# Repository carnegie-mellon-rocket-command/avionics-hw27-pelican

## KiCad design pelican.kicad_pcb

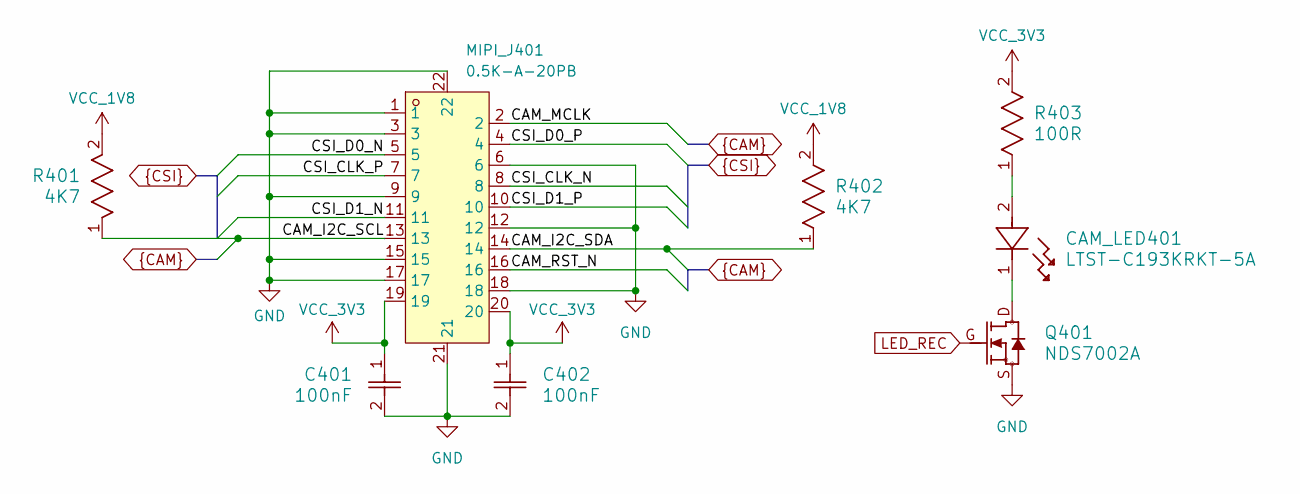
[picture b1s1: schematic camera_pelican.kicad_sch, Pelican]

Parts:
C401, C402: 100nF; C_GRM155R71C104KA88D; LCSC Part # C71629
CAM_LED401: LTST-C193KRKT-5A; LED_LTST-C193KRKT-5A; LCSC Part # C157741
MIPI_J401: 0.5K-A-20PB; J_0.5K-A-20PB; MPN 0.5K-A-20PB; LCSC Part C2914144
Q401: NDS7002A; Q_NDS7002A; LCSC Part # C74715
R401, R402: 4K7; R_RC0402FR; LCSC Part # C105871
R403: 100R; R_RC0402FR; LCSC Part # C106232

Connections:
CAM_I2C_SCL: MIPI_J401.13, R401.1; also elsewhere on the board
CAM_I2C_SDA: MIPI_J401.14, R402.1; also elsewhere on the board
CAM_MCLK: MIPI_J401.2; also elsewhere on the board
CAM_RST_N: MIPI_J401.16; also elsewhere on the board
CSI_CLK_N: MIPI_J401.8; also elsewhere on the board
CSI_CLK_P: MIPI_J401.7; also elsewhere on the board
CSI_D0_N: MIPI_J401.5; also elsewhere on the board
CSI_D0_P: MIPI_J401.4; also elsewhere on the board
CSI_D1_N: MIPI_J401.11; also elsewhere on the board
CSI_D1_P: MIPI_J401.10; also elsewhere on the board
GND: C401.2, C402.2, MIPI_J401.1, MIPI_J401.3, MIPI_J401.6, MIPI_J401.9, MIPI_J401.12, MIPI_J401.15, MIPI_J401.17, MIPI_J401.18, MIPI_J401.21, MIPI_J401.22, Q401.S; also elsewhere on the board
LED_REC: Q401.G; also elsewhere on the board
unnamed: CAM_LED401.1, Q401.D
unnamed: CAM_LED401.2, R403.1
VCC_1V8: R401.2, R402.2; also elsewhere on the board
VCC_3V3: C401.1, C402.1, MIPI_J401.19, MIPI_J401.20, R403.2; also elsewhere on the board

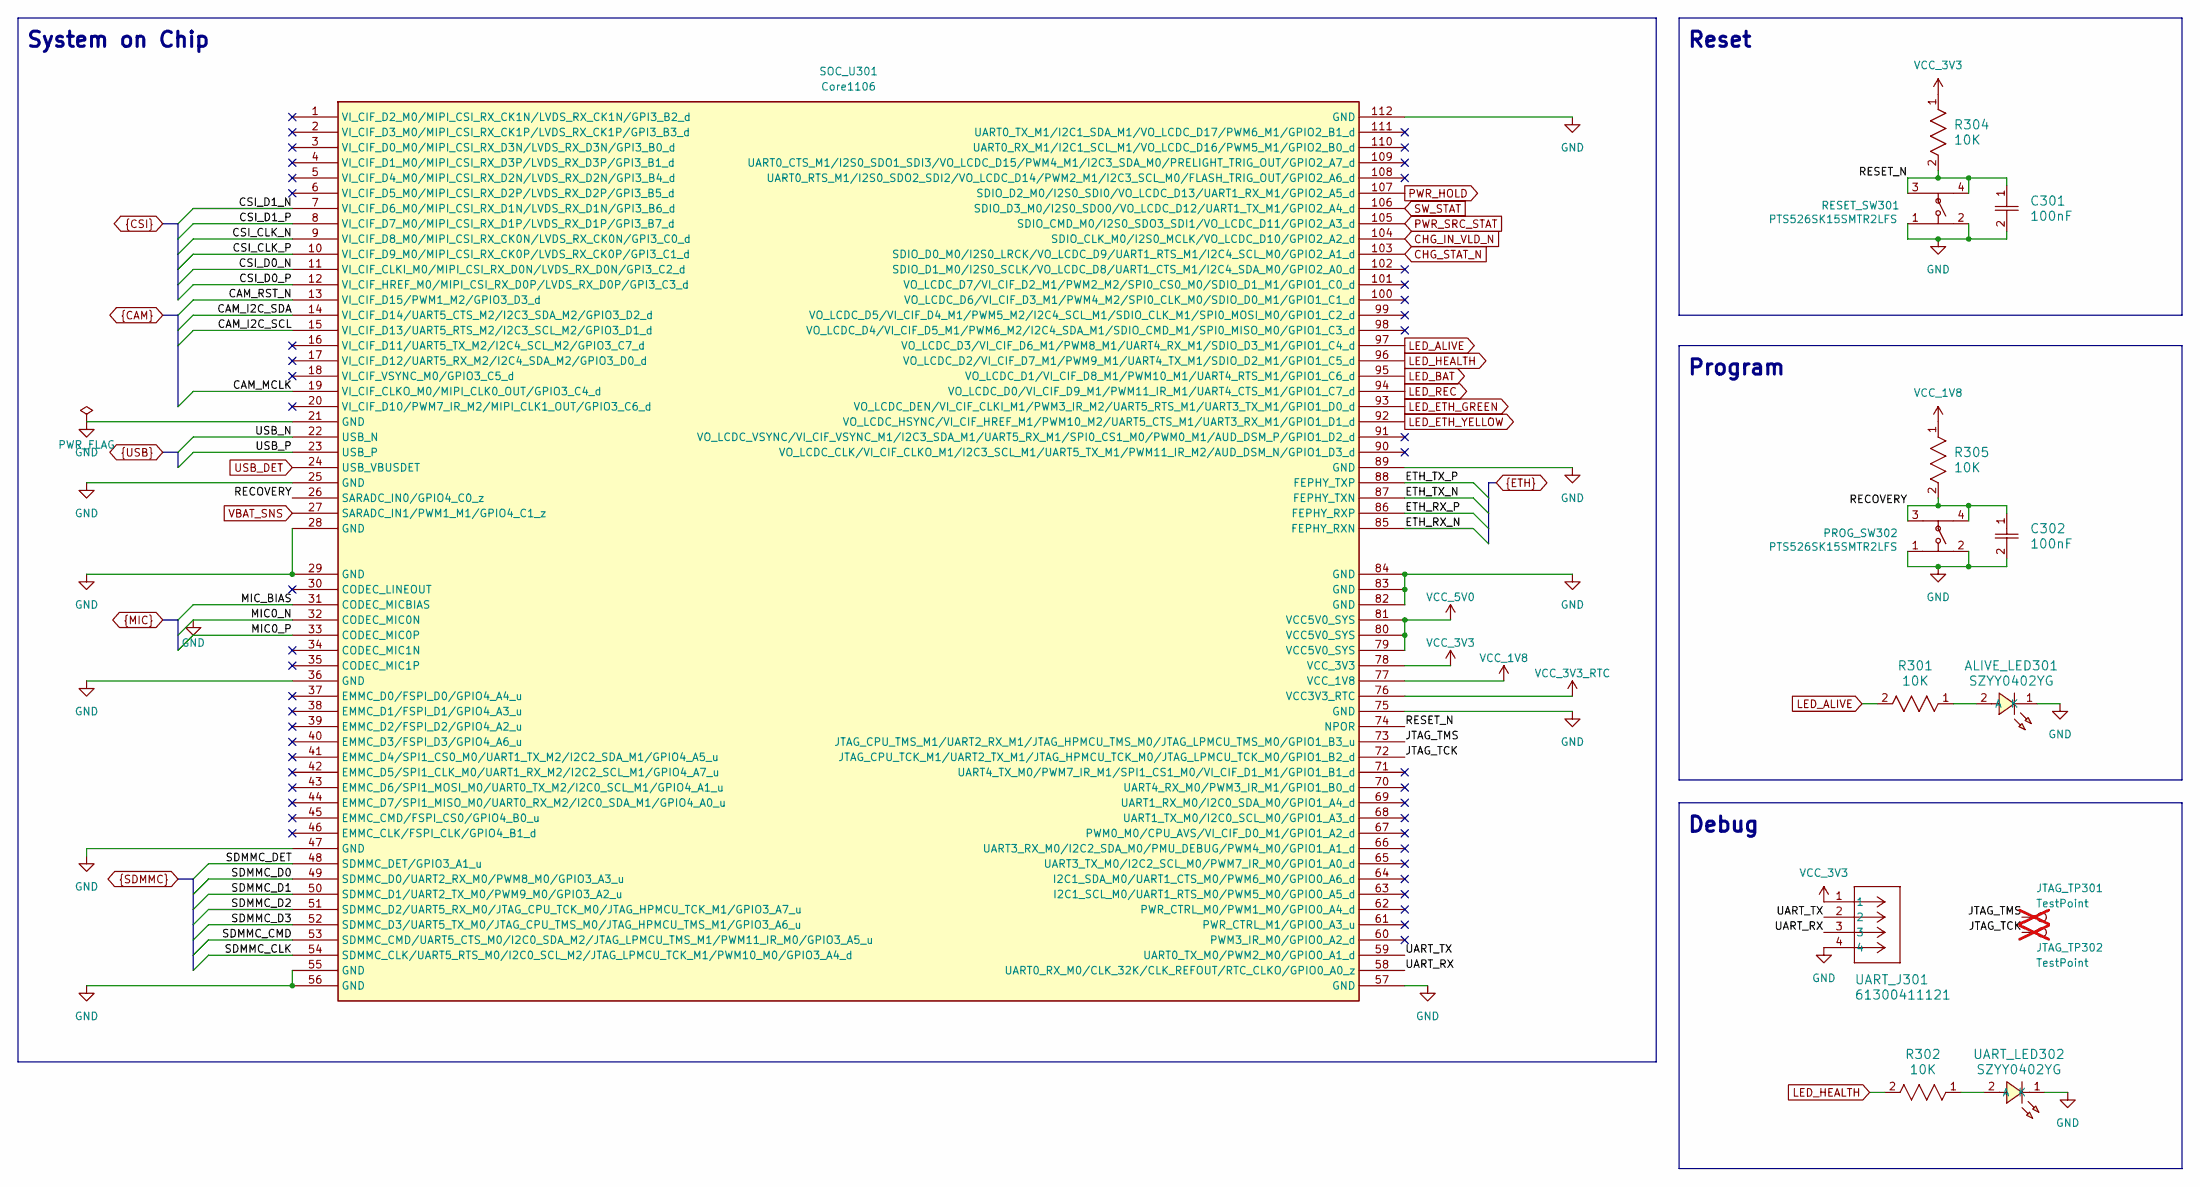
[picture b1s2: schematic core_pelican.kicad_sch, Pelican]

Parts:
ALIVE_LED301: SZYY0402YG; LED_SZYY0402YG; MPN SZYY0402YG; LCSC Part # C434449
C301, C302: 100nF; C_GRM155R71C104KA88D; LCSC Part # C71629
JTAG_TP301, JTAG_TP302: TestPoint; TestPoint_Pad_D1.5mm; not fitted
PROG_SW302: PTS526SK15SMTR2LFS; SW_PTS526SK15SMTR2LFS; LCSC Part # C2689521
R301, R302, R304, R305: 10K; R_RC0402FR; LCSC Part # C60490
RESET_SW301: PTS526SK15SMTR2LFS; SW_PTS526SK15SMTR2LFS; LCSC Part # C2689521
SOC_U301: Core1106; P_Core1106
UART_J301: 61300411121; J_61300411121; LCSC Part # C5184785
UART_LED302: SZYY0402YG; LED_SZYY0402YG; MPN SZYY0402YG; LCSC Part # C434449

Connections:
/Core/JTAG_TCK: JTAG_TP302.1 (1_1), SOC_U301.72 (JTAG_CPU_TCK_M1/UART2_TX_M1/JTAG_HPMCU_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)
/Core/JTAG_TMS: JTAG_TP301.1 (1_1), SOC_U301.73 (JTAG_CPU_TMS_M1/UART2_RX_M1/JTAG_HPMCU_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)
/Core/RECOVERY: C302.1, PROG_SW302.3, PROG_SW302.4, R305.2, SOC_U301.26 (SARADC_IN0/GPIO4_C0_z)
/Core/RESET_N: C301.1, R304.2, RESET_SW301.3, RESET_SW301.4, SOC_U301.74 (NPOR)
/Core/UART_RX: SOC_U301.58 (UART0_RX_M0/CLK_32K/CLK_REFOUT/RTC_CLKO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), UART_J301.3; also elsewhere on the board
/Core/UART_TX: SOC_U301.59 (UART0_TX_M0/PWM2_M0/GPIO0_A1_d), UART_J301.2; also elsewhere on the board
CAM_I2C_SCL: SOC_U301.15 (VI_CIF_D13/UART5_RTS_M2/I2C3_SCL_M2/GPI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); also elsewhere on the board
CAM_I2C_SDA: SOC_U301.14 (VI_CIF_D14/UART5_CTS_M2/I2C3_SDA_M2/GPI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); also elsewhere on the board
CAM_MCLK: SOC_U301.19 (VI_CIF_CLKO_M0/MIPI_CLK0_OUT/GPIO3_C4_d); also elsewhere on the board
CAM_RST_N: SOC_U301.13 (VI_CIF_D15/PWM1_M2/GPIO3_D3_d); also elsewhere on the board
CHG_IN_VLD_N: SOC_U301.104 (SDIO_CLK_M0/I2S0_MCLK/VO_LCDC_D10/GPIO2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); also elsewhere on the board
CHG_STAT_N: SOC_U301.103 (SDIO_D0_M0/I2S0_LRCK/VO_LCDC_D9/UART1_R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); also elsewhere on the board
CSI_CLK_N: SOC_U301.9 (VI_CIF_D8_M0/MIPI_CSI_RX_CK0N/LVDS_RX_C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); also elsewhere on the board
CSI_CLK_P: SOC_U301.10 (VI_CIF_D9_M0/MIPI_CSI_RX_CK0P/LVDS_RX_C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); also elsewhere on the board
CSI_D0_N: SOC_U301.11 (VI_CIF_CLKI_M0/MIPI_CSI_RX_D0N/LVDS_RX_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); also elsewhere on the board
CSI_D0_P: SOC_U301.12 (VI_CIF_HREF_M0/MIPI_CSI_RX_D0P/LVDS_RX_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); also elsewhere on the board
CSI_D1_N: SOC_U301.7 (VI_CIF_D6_M0/MIPI_CSI_RX_D1N/LVDS_RX_D1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); also elsewhere on the board
CSI_D1_P: SOC_U301.8 (VI_CIF_D7_M0/MIPI_CSI_RX_D1P/LVDS_RX_D1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); also elsewhere on the board
ETH_RX_N: SOC_U301.85 (FEPHY_RXN); also elsewhere on the board
ETH_RX_P: SOC_U301.86 (FEPHY_RXP); also elsewhere on the board
ETH_TX_N: SOC_U301.87 (FEPHY_TXN); also elsewhere on the board
ETH_TX_P: SOC_U301.88 (FEPHY_TXP); also elsewhere on the board
GND: ALIVE_LED301.1 (K), C301.2, C302.2, PROG_SW302.1, PROG_SW302.2, RESET_SW301.1, RESET_SW301.2, SOC_U301.21 (GND), SOC_U301.25 (GND), SOC_U301.28 (GND), SOC_U301.29 (GND), SOC_U301.32 (CODEC_MIC0N), SOC_U301.36 (GND), SOC_U301.47 (GND), SOC_U301.55 (GND), SOC_U301.56 (GND), SOC_U301.57 (GND), SOC_U301.75 (GND), SOC_U301.82 (GND), SOC_U301.83 (GND), SOC_U301.84 (GND), SOC_U301.89 (GND), SOC_U301.112 (GND), UART_J301.4, UART_LED302.1 (K); also elsewhere on the board
LED_ALIVE: R301.2, SOC_U301.97 (VO_LCDC_D3/VI_CIF_D6_M1/PWM8_M1/UART4_R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)
LED_BAT: SOC_U301.95 (VO_LCDC_D1/VI_CIF_D8_M1/PWM10_M1/UART4_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); also elsewhere on the board
LED_ETH_GREEN: SOC_U301.93 (VO_LCDC_DEN/VI_CIF_CLKI_M1/PWM3_IR_M2/U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); also elsewhere on the board
LED_ETH_YELLOW: SOC_U301.92 (VO_LCDC_HSYNC/VI_CIF_HREF_M1/PWM10_M2/U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); also elsewhere on the board
LED_HEALTH: R302.2, SOC_U301.96 (VO_LCDC_D2/VI_CIF_D7_M1/PWM9_M1/UART4_T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)
LED_REC: SOC_U301.94 (VO_LCDC_D0/VI_CIF_D9_M1/PWM11_IR_M1/UAR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); also elsewhere on the board
MIC0_P: SOC_U301.33 (CODEC_MIC0P); also elsewhere on the board
MIC_BIAS: SOC_U301.31 (CODEC_MICBIAS); also elsewhere on the board
unnamed: ALIVE_LED301.2 (A), R301.1
unnamed: R302.1, UART_LED302.2 (A)
PWR_HOLD: SOC_U301.107 (SDIO_D2_M0/I2S0_SDI0/VO_LCDC_D13/UART1_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); also elsewhere on the board
PWR_SRC_STAT: SOC_U301.105 (SDIO_CMD_M0/I2S0_SDO3_SDI1/VO_LCDC_D11/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); also elsewhere on the board
SDMMC_CLK: SOC_U301.54 (SDMMC_CLK/UART5_RTS_M0/I2C0_SCL_M2/JTAG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); also elsewhere on the board
SDMMC_CMD: SOC_U301.53 (SDMMC_CMD/UART5_CTS_M0/I2C0_SDA_M2/JTAG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); also elsewhere on the board
SDMMC_D0: SOC_U301.49 (SDMMC_D0/UART2_RX_M0/PWM8_M0/GPIO3_A3_u); also elsewhere on the board
SDMMC_D1: SOC_U301.50 (SDMMC_D1/UART2_TX_M0/PWM9_M0/GPIO3_A2_u); also elsewhere on the board
SDMMC_D2: SOC_U301.51 (SDMMC_D2/UART5_RX_M0/JTAG_CPU_TCK_M0/JT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); also elsewhere on the board
SDMMC_D3: SOC_U301.52 (SDMMC_D3/UART5_TX_M0/JTAG_CPU_TMS_M0/JT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); also elsewhere on the board
SDMMC_DET: SOC_U301.48 (SDMMC_DET/GPIO3_A1_u); also elsewhere on the board
SW_STAT: SOC_U301.106 (SDIO_D3_M0/I2S0_SDO0/VO_LCDC_D12/UART1_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); also elsewhere on the board
USB_DET: SOC_U301.24 (USB_VBUSDET); also elsewhere on the board
USB_N: SOC_U301.22 (USB_N); also elsewhere on the board
USB_P: SOC_U301.23 (USB_P); also elsewhere on the board
VBAT_SNS: SOC_U301.27 (SARADC_IN1/PWM1_M1/GPIO4_C1_z); also elsewhere on the board
VCC_1V8: R305.1, SOC_U301.77 (VCC_1V8); also elsewhere on the board
VCC_3V3: R304.1, SOC_U301.78 (VCC_3V3), UART_J301.1; also elsewhere on the board
VCC_3V3_RTC: SOC_U301.76 (VCC3V3_RTC)
VCC_5V0: SOC_U301.79 (VCC5V0_SYS), SOC_U301.80 (VCC5V0_SYS), SOC_U301.81 (VCC5V0_SYS); also elsewhere on the board

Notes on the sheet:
Debug
System on Chip
Program
Reset

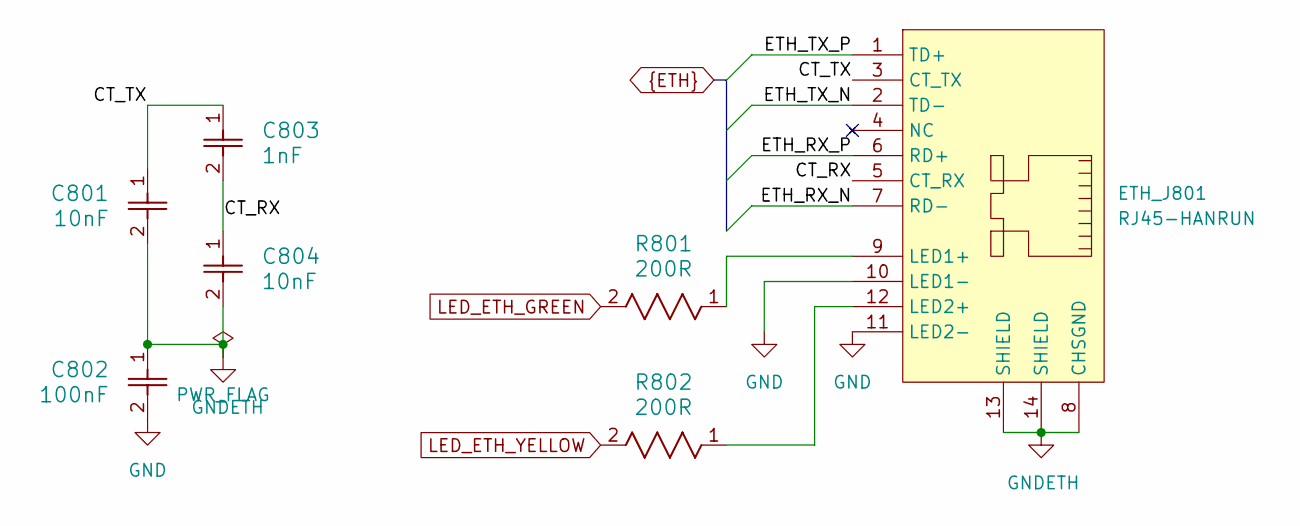
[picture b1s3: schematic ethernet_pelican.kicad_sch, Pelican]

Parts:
C801, C804: 10nF; C_CL05B103KO5NNNC; MPN CL05B103KO5NNNC; LCSC Part # C318577
C802: 100nF; C_GRM155R71C104KA88D; LCSC Part # C71629
C803: 1nF; C_CC0603CG100V102JN; MPN CC0603CG100V102JN; LCSC Part # C53084479
ETH_J801: RJ45-HANRUN; J_RJ45-HANRUN_TH; MPN HY951180A; LCSC Part # C34677
R801, R802: 200R; R_RC0402FR

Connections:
/Ethernet/CT_RX: C803.2, C804.1, ETH_J801.5 (CT_RX); also elsewhere on the board
/Ethernet/CT_TX: C801.1, C803.1, ETH_J801.3 (CT_TX); also elsewhere on the board
GND: C802.2, ETH_J801.10 (LED1-), ETH_J801.11 (LED2-); also elsewhere on the board
GNDETH: C801.2, C802.1, C804.2, ETH_J801.8 (CHSGND), ETH_J801.13 (SHIELD), ETH_J801.14 (SHIELD); also elsewhere on the board
LED_ETH_GREEN: R801.2; also elsewhere on the board
LED_ETH_YELLOW: R802.2; also elsewhere on the board
unnamed 51: ETH_J801.9 (LED1+), R801.1; also elsewhere on the board
unnamed 52: ETH_J801.12 (LED2+), R802.1; also elsewhere on the board

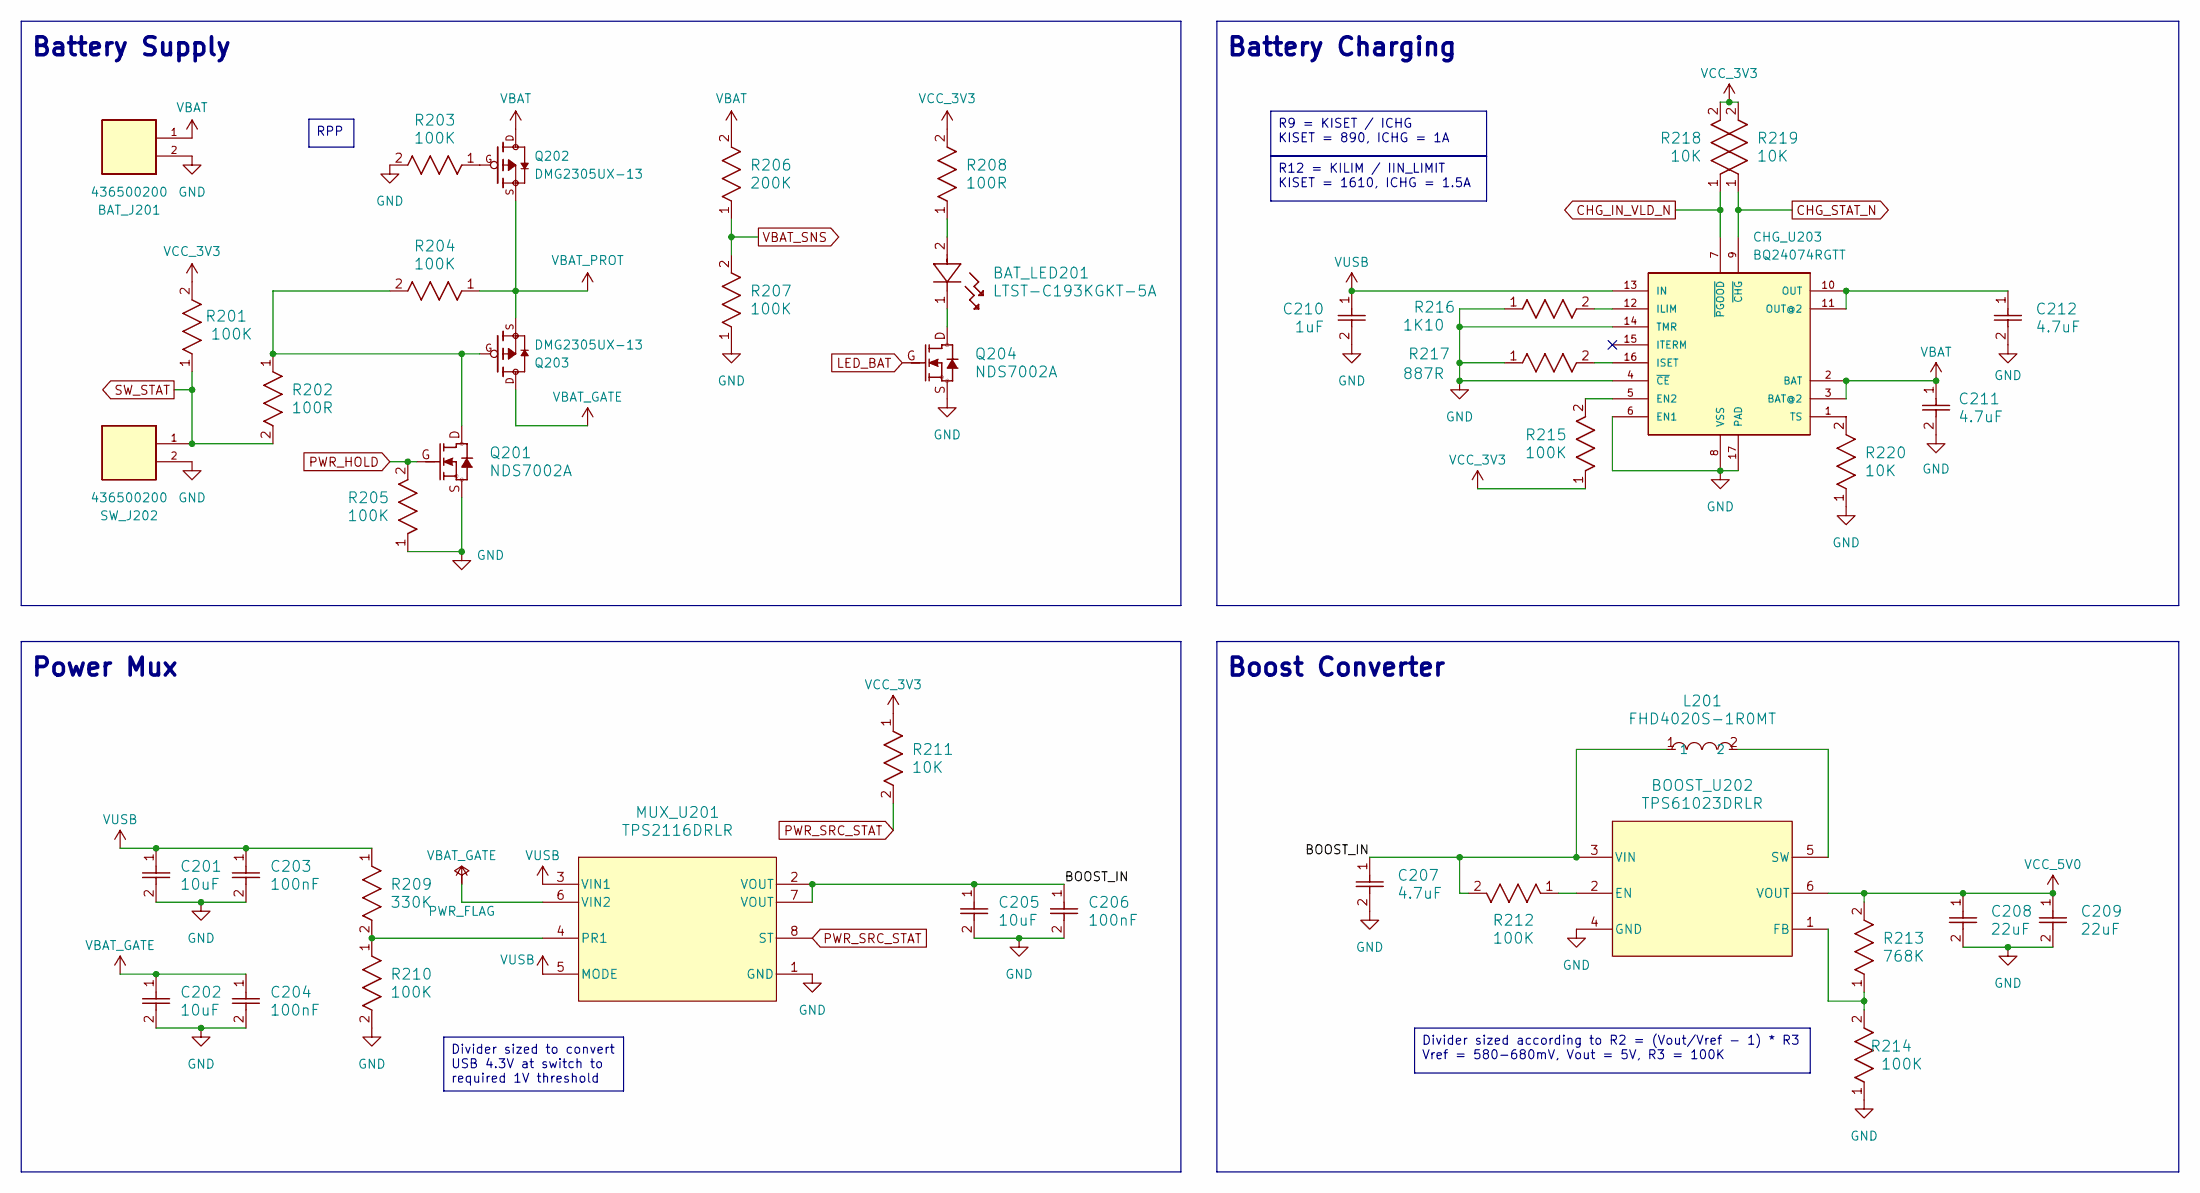
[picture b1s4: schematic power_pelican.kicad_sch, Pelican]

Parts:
BAT_J201: 436500200; J_436500200; MANUFACTURER_PART_NUMBER 436500200; LCSC Part # C192562
BAT_LED201: LTST-C193KGKT-5A; LED_LTST-C193KGKT-5A; LCSC Part # C125102
BOOST_U202: TPS61023DRLR; U_TPS61023DRLR; LCSC Part # C919459
C201, C202, C205: 10uF; C_GRM155R61A106ME11D; LCSC Part # C408132
C203, C204, C206: 100nF; C_GRM155R71C104KA88D; LCSC Part # C71629
C207, C211, C212: 4.7uF; C_GRM188R61A475KE15D; LCSC Part # C71633
C208, C209: 22uF; C_GRM188R61A226ME15D; LCSC Part # C84419
C210: 1uF; C_GRM155R61A105KE15D; LCSC Part # C76999
CHG_U203: BQ24074RGTT; U_BQ24074RGTT; LCSC Part # C2861252
L201: FHD4020S-1R0MT; L_FHD4020S-1R0MT; MPN FHD4020S-1R0MT; LCSC Part # C602028
MUX_U201: TPS2116DRLR; U_TPS2116DRLR; LCSC Part # C3235557
Q201, Q204: NDS7002A; Q_NDS7002A; LCSC Part # C74715
Q202, Q203: DMG2305UX-13; Q_DMG2305UX-13; PARTREV 09/2018; LCSC Part # C144153
R201: 100K; R_RC0402FR; LCSC Part # C60490
R202, R208: 100R; R_RC0402FR; LCSC Part # C106232
R203, R204, R205, R207, R210, R212, R214, R215: 100K; R_RC0402FR; LCSC Part # C60491
R206: 200K; R_RC0402FR; LCSC Part # C114763
R209: 330K; R_RC0402FR; LCSC Part # C25778
R211, R218, R219, R220: 10K; R_RC0402FR; LCSC Part # C60490
R213: 768K; R_RC0402FR; LCSC Part # C273722
R216: 1K10; R_RC0402FR; LCSC Part # C25860
R217: 887R; R_RC0402FR; LCSC Part # C477810
SW_J202: 436500200; J_436500200; MANUFACTURER_PART_NUMBER 436500200; LCSC Part # C192562

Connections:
/Power/BOOST_IN: BOOST_U202.3 (VIN), C205.1, C206.1, C207.1, L201.1, MUX_U201.2 (VOUT), MUX_U201.7 (VOUT), R212.2
CHG_IN_VLD_N: CHG_U203.7 (~PGOOD), R218.1; also elsewhere on the board
CHG_STAT_N: CHG_U203.9 (~CHG), R219.1; also elsewhere on the board
GND: BAT_J201.2, BOOST_U202.4 (GND), C201.2, C202.2, C203.2, C204.2, C205.2, C206.2, C207.2, C208.2, C209.2, C210.2, C211.2, C212.2, CHG_U203.4 (~CE), CHG_U203.6 (EN1), CHG_U203.8 (VSS), CHG_U203.14 (TMR), CHG_U203.17 (PAD), MUX_U201.1 (GND), Q201.S, Q204.S, R203.2, R205.1, R207.1, R210.2, R214.1, R216.1, R217.1, R220.1, SW_J202.2; also elsewhere on the board
LED_BAT: Q204.G; also elsewhere on the board
unnamed: BAT_LED201.1, Q204.D
unnamed: BAT_LED201.2, R208.1
unnamed: BOOST_U202.2 (EN), R212.1
unnamed: BOOST_U202.1 (FB), R213.1, R214.2
unnamed: BOOST_U202.5 (SW), L201.2
unnamed: CHG_U203.5 (EN2), R215.2
unnamed: CHG_U203.12 (ILIM), R216.2
unnamed: CHG_U203.16 (ISET), R217.2
unnamed: C212.1, CHG_U203.10 (OUT), CHG_U203.11 (OUT@2)
unnamed: CHG_U203.1 (TS), R220.2
unnamed: MUX_U201.4 (PR1), R209.2, R210.1
unnamed: Q201.D, Q203.G, R202.1, R204.2
unnamed: Q202.G, R203.1
unnamed: Q202.S, Q203.S, R204.1
PWR_HOLD: Q201.G, R205.2; also elsewhere on the board
PWR_SRC_STAT: MUX_U201.8 (ST), R211.2; also elsewhere on the board
SW_STAT: R201.1, R202.2, SW_J202.1; also elsewhere on the board
VBAT: BAT_J201.1, C211.1, CHG_U203.2 (BAT), CHG_U203.3 (BAT@2), Q202.D, R206.2; also elsewhere on the board
VBAT_GATE: C202.1, C204.1, MUX_U201.6 (VIN2), Q203.D
VBAT_SNS: R206.1, R207.2; also elsewhere on the board
VCC_3V3: R201.2, R208.2, R211.1, R215.1, R218.2, R219.2; also elsewhere on the board
VCC_5V0: BOOST_U202.6 (VOUT), C208.1, C209.1, R213.2; also elsewhere on the board
VUSB: C201.1, C203.1, C210.1, CHG_U203.13 (IN), MUX_U201.3 (VIN1), MUX_U201.5 (MODE), R209.1; also elsewhere on the board

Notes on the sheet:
Battery Charging
Power Mux
Battery Supply
Boost Converter
Divider sized according to R2 = (Vout/Vref - 1) * R3 Vref = 580-680mV, Vout = 5V, R3 = 100K
R12 = KILIM / IIN_LIMIT KISET = 1610, ICHG = 1.5A
R9 = KISET / ICHG KISET = 890, ICHG = 1A
Divider sized to convert USB 4.3V at switch to required 1V threshold
RPP

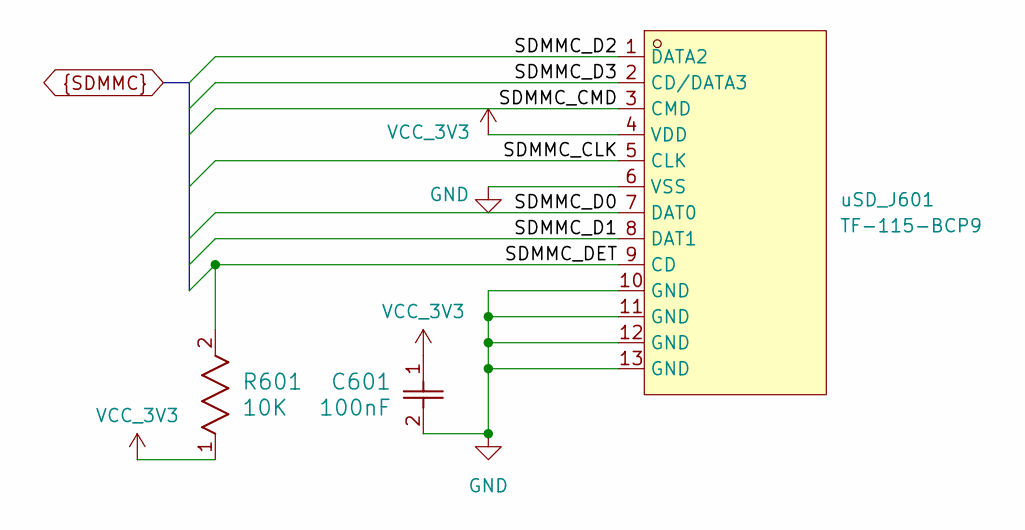
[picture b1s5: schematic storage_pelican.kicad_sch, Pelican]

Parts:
C601: 100nF; C_GRM155R71C104KA88D; LCSC Part # C71629
R601: 10K; R_RC0402FR; LCSC Part # C60490
uSD_J601: TF-115-BCP9; J_TF-115-BCP9; MPN TF-115-BCP9; LCSC Part # C720505

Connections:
GND: C601.2, uSD_J601.6 (VSS), uSD_J601.10 (GND), uSD_J601.11 (GND), uSD_J601.12 (GND), uSD_J601.13 (GND); also elsewhere on the board
SDMMC_CLK: uSD_J601.5 (CLK); also elsewhere on the board
SDMMC_CMD: uSD_J601.3 (CMD); also elsewhere on the board
SDMMC_D0: uSD_J601.7 (DAT0); also elsewhere on the board
SDMMC_D1: uSD_J601.8 (DAT1); also elsewhere on the board
SDMMC_D2: uSD_J601.1 (DATA2); also elsewhere on the board
SDMMC_D3: uSD_J601.2 (CD/DATA3); also elsewhere on the board
SDMMC_DET: R601.2, uSD_J601.9 (CD); also elsewhere on the board
VCC_3V3: C601.1, R601.1, uSD_J601.4 (VDD); also elsewhere on the board

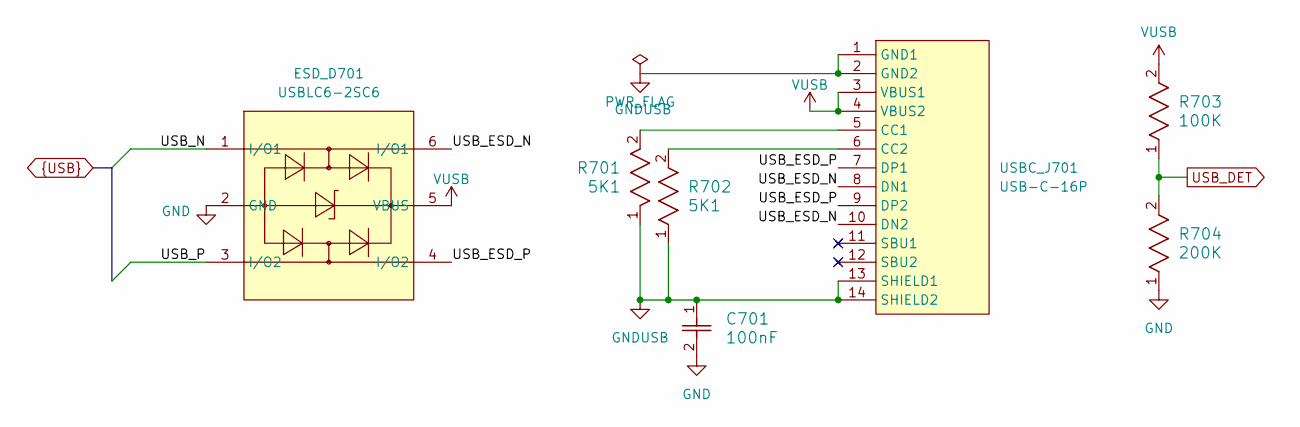
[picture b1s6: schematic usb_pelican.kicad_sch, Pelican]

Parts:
C701: 100nF; C_GRM155R71C104KA88D; LCSC Part # C71629
ESD_D701: USBLC6-2SC6; D_USBLC6-2SC6; MPN USBLC6-2SC6; LCSC Part # C7519
R701, R702: 5K1; R_RC0402FR; LCSC Part # C105872
R703: 100K; R_RC0402FR; LCSC Part # C60491
R704: 200K; R_RC0402FR; LCSC Part # C114763
USBC_J701: USB-C-16P; J_USB-C-16P_SMD; MPN TYPE-C 16P LTH6.8; LCSC Part # C5187468

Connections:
/USB/USB_ESD_N: ESD_D701.6 (I/O1), USBC_J701.8 (DN1), USBC_J701.10 (DN2); also elsewhere on the board
/USB/USB_ESD_P: ESD_D701.4 (I/O2), USBC_J701.7 (DP1), USBC_J701.9 (DP2); also elsewhere on the board
GND: C701.2, ESD_D701.2 (GND), R704.1; also elsewhere on the board
GNDUSB: C701.1, R701.1, R702.1, USBC_J701.1 (GND1), USBC_J701.2 (GND2), USBC_J701.13 (SHIELD1), USBC_J701.14 (SHIELD2); also elsewhere on the board
unnamed 59: R701.2, USBC_J701.5 (CC1); also elsewhere on the board
unnamed 60: R702.2, USBC_J701.6 (CC2); also elsewhere on the board
USB_DET: R703.1, R704.2; also elsewhere on the board
USB_N: ESD_D701.1 (I/O1); also elsewhere on the board
USB_P: ESD_D701.3 (I/O2); also elsewhere on the board
VUSB: ESD_D701.5 (VBUS), R703.2, USBC_J701.3 (VBUS1), USBC_J701.4 (VBUS2); also elsewhere on the board

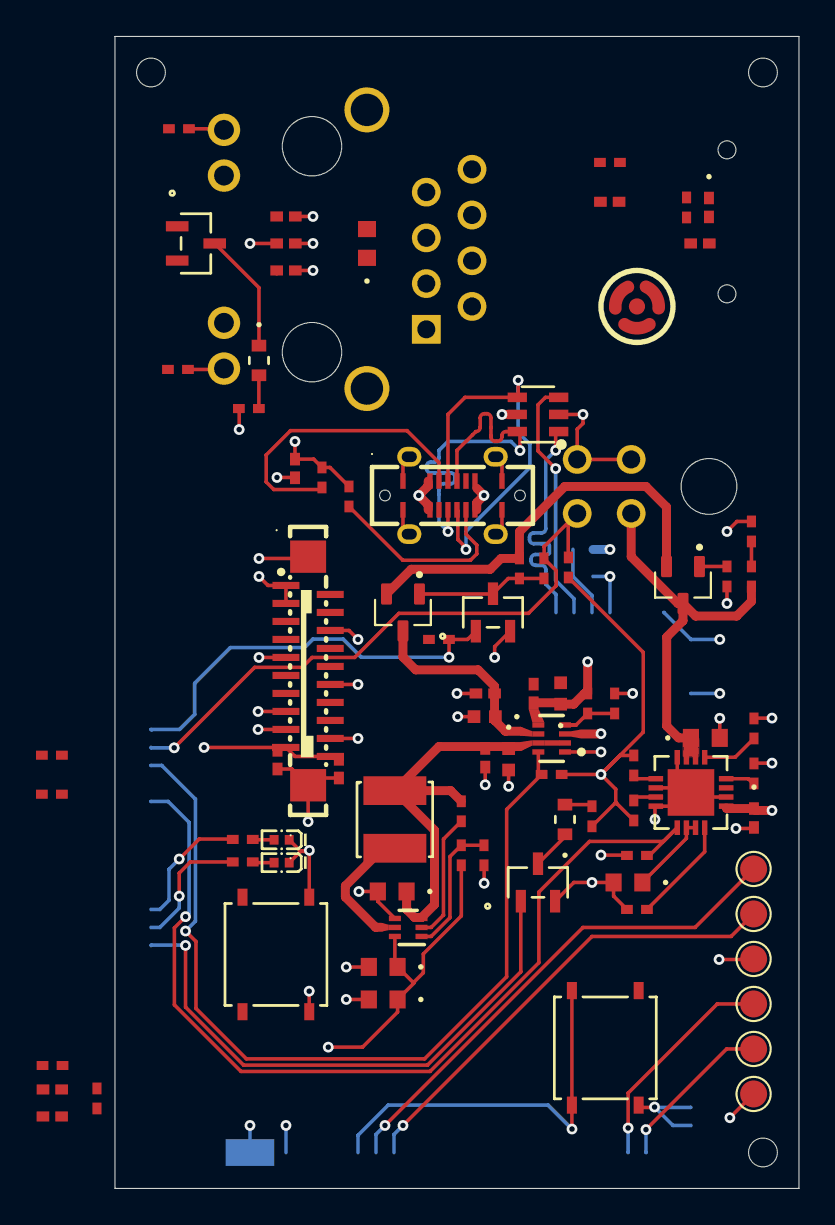
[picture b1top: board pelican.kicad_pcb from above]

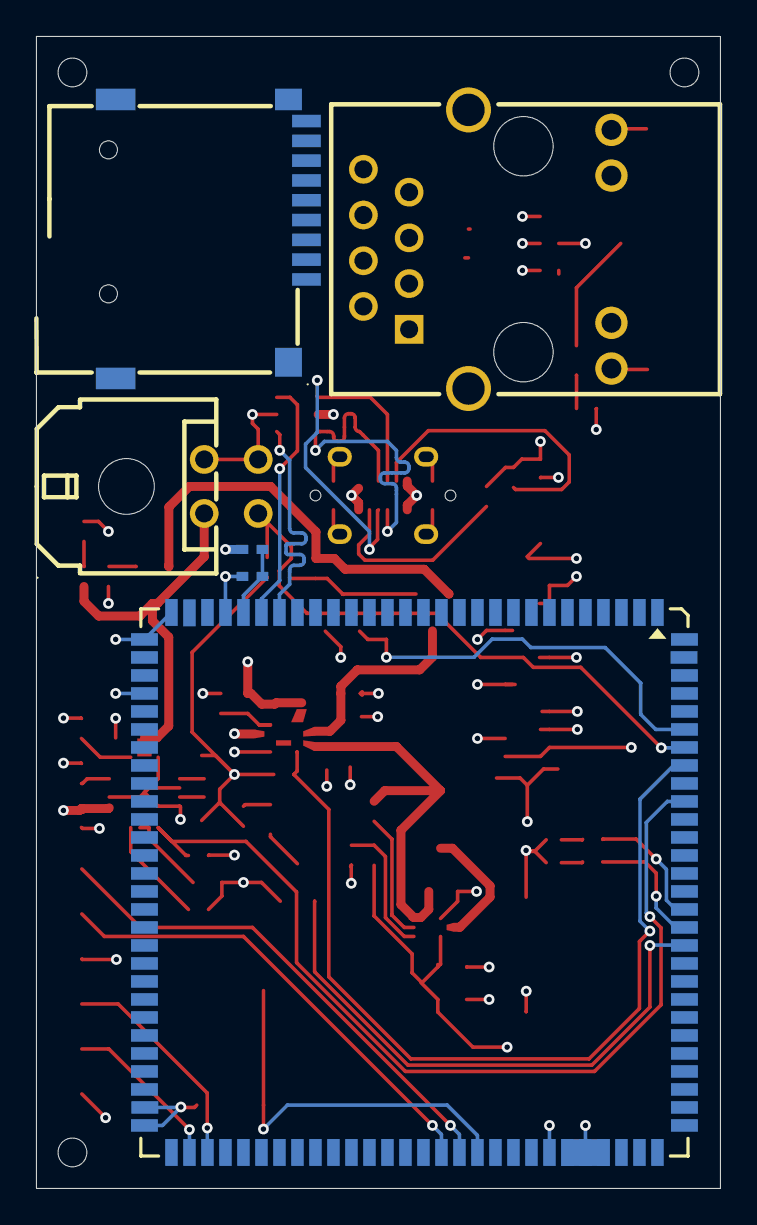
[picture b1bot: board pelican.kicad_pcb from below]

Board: 4 copper layers, 38.0 x 64.0 mm, 88 parts (6 on the bottom side), 81 nets.

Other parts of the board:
C501: 100nF; C_GRM155R71C104KA88D
C502: 1uF; C_GRM155R61A105KE15D
CN201: 43045-0401; J_43045-0401_2x02_RA
J801: HR911105A; J_HR911105A_TH
MIC_M501: MIC4013-X; M_MIC4013-X
R501: 2K2; R_RC0402FR
UART_TP303, UART_TP304, UART_TP305, UART_TP306: TestPoint; TestPoint_Pad_D1.5mm
USB701: USB4120-03-C; J_USB4120-03-C_SMD

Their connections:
/Core/UART_RX: UART_TP305.1 (1_1); also elsewhere on the board
/Core/UART_TX: UART_TP304.1 (1_1); also elsewhere on the board
/Ethernet/CT_RX: J801.5 (CT_RX); also elsewhere on the board
/Ethernet/CT_TX: J801.4 (CT_TX); also elsewhere on the board
/USB/USB_ESD_N: USB701.A7 (DN1), USB701.B7 (DN2); also elsewhere on the board
/USB/USB_ESD_P: USB701.A6 (DP1), USB701.B6 (DP2); also elsewhere on the board
ETH_RX_N: J801.6 (RD-); also elsewhere on the board
ETH_RX_P: J801.3 (RD+); also elsewhere on the board
ETH_TX_N: J801.2 (TD-); also elsewhere on the board
ETH_TX_P: J801.1 (TD+); also elsewhere on the board
GND: C501.2, CN201.2, CN201.4, J801.10 (LED1-), J801.11 (LED2-), MIC_M501.2 (-), UART_TP306.1 (1_1); also elsewhere on the board
GNDETH: J801.8 (CHSGND), J801.SH1 (SHIELD), J801.SH2 (SHIELD); also elsewhere on the board
GNDUSB: USB701.0 (SHIELD), USB701.A1 (GND1), USB701.A12 (GND3), USB701.B1 (GND2), USB701.B12 (GND4); also elsewhere on the board
MIC0_P: C502.2; also elsewhere on the board
MIC_BIAS: C501.1, R501.2; also elsewhere on the board
unnamed 51: J801.9 (LED1+); also elsewhere on the board
unnamed 52: J801.12 (LED2+); also elsewhere on the board
unnamed: C502.1, MIC_M501.1 (+), R501.1
unnamed 59: USB701.A5 (CC1); also elsewhere on the board
unnamed 60: USB701.B5 (CC2); also elsewhere on the board
SW_STAT: CN201.3; also elsewhere on the board
VBAT: CN201.1; also elsewhere on the board
VCC_3V3: UART_TP303.1 (1_1); also elsewhere on the board
VUSB: USB701.A4 (VBUS1), USB701.A9 (VBUS3), USB701.B4 (VBUS2), USB701.B9 (VBUS4); also elsewhere on the board
